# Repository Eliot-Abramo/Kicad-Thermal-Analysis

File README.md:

# TVAC Thermal Analyzer v4.0

**Physically rigorous thermal analysis for PCBs operating in Thermal Vacuum (TVAC) conditions.**

Reads KiCad 9 `.kicad_pcb` files directly — no KiCad or pcbnew dependency required. Generates adaptive thermal meshes with via modeling, solves steady-state and transient heat conduction with radiation, and displays interactive results with per-layer visualization.

## Quick Start

```bash
chmod +x build.sh
./build.sh                              # install deps + compile C engine
python3 tvac_analyzer.py                # opens file dialog
python3 tvac_analyzer.py board.kicad_pcb  # open specific file
```

## Requirements

| Dependency | Purpose |
|-----------|---------|
| Python 3.8+ | Runtime |
| PyQt5 | GUI |
| NumPy | Mesh & arrays |
| SciPy | Sparse solver (fallback) |
| GCC (optional) | C thermal engine (3-5× faster) |

Install: `pip install PyQt5 numpy scipy`

## What's New in v4

### Physics Improvements
- **Adaptive mesh refinement** — quadtree-based, fine cells (0.15mm) near vias/pads/heat sources, coarse cells (3mm) in bulk FR4
- **Explicit via thermal modeling** — barrel conductance G = k_cu · A_barrel / L bridges copper layers
- **Proper copper fraction** — per-cell computation from filled zones, traces, and via pads
- **Linearized radiation Picard** — adds 4·ε·σ·T³·A to diagonal for dramatically faster convergence
- **Separate top/bottom emissivity** — solder mask (ε=0.90) on exposed surfaces, none on internal layers
- **Energy balance verification** — tracks input power vs radiation + conduction losses
- **IC(0) preconditioner** — Incomplete Cholesky with automatic Jacobi fallback

### KiCad 9 Support
- `filled_polygon` zones (actual copper fill geometry)
- `property` nodes for Reference/Value
- Arc trace support (`arc` with start/mid/end)
- Pad mirroring for back-side components
- Stackup parsing for per-layer copper thickness

### Performance
- OpenMP parallelization in C engine
- Adaptive mesh reduces node count ~75% vs uniform at same accuracy
- Anderson acceleration for Picard iteration
- Adaptive under-relaxation (ω: 0.15 → 0.95)

## Features

### 5-Tab Interface

1. **Components** — Click any component to set power dissipation. Filter by prefix (U*, Q*, R*). Auto-imports `POWER_DISSIPATION` fields from KiCad.

2. **Heatsinks** — Define heatsink polygons with material selection (Aluminum 6061/6063, Anodized Al, Copper). Set thickness and emissivity.

3. **Mounting Points** — Auto-detect mounting holes. Set fixed-temperature boundary conditions.

4. **Current Path** — Define source/sink net pairs for I²R Joule heating analysis. Temperature-dependent copper resistivity.

5. **Simulation** — Heat source mode, analysis type, environment temps, mesh resolution, adaptive settings, radiation toggle.

### Interactive PCB Visualization

- Pan (drag) and zoom (scroll wheel) the board
- Click components to select and edit power
- Per-layer toggles: Grid, Outline, Top Cu, Bottom Cu, Inner Cu, Traces, Vias, Heatsinks, Mounting, Thermal overlay
- Layer-specific colors: F.Cu=red, B.Cu=blue, inner layers=yellow/green
- Thermal heatmap overlay with Blue→Cyan→Green→Yellow→Red gradient

### Dual Solver Backend

| Backend | Speed | Features | Availability |
|---------|-------|----------|-------------|
| **C Engine** | ~0.03s typical | IC(0) preconditioner, OpenMP, Anderson accel | Requires GCC |
| **SciPy** | ~0.15s typical | Direct solver + Picard | Always available |

Both backends produce identical physics — validated to < 0.01°C difference.

### Physics Model

- **Conduction**: Harmonic mean k_eff for series resistance, copper fraction blending
- **Radiation**: Stefan-Boltzmann with separate top/bottom surface emissivity
- **Vias**: Barrel conductance bridging copper layers (G = k_cu · A / L)
- **Picard iteration**: Linearized radiation with adaptive under-relaxation
- **Copper blending**: k_eff = f·k_cu + (1-f)·k_FR4 with fraction from zones/traces/pads
- **I²R heating**: Temperature-dependent resistivity ρ(T) = ρ₀·(1 + α·ΔT)
- **Transient**: Crank-Nicolson (θ=0.5), 2nd-order time accuracy

## File Structure

```
tvac_analyzer/
├── tvac_analyzer.py          # Complete standalone application (~3700 lines)
├── thermal_engine.c          # Optimized C solver with IC(0) + OpenMP
├── libthermal_engine.so      # Compiled C library (auto-generated)
├── build.sh                  # Build & dependency installer
└── README.md                 # This file
```

## Configuration

Settings auto-save to `<board>.tvac_config.json` alongside the PCB file. Config includes:
- Component power assignments
- Heatsink definitions with polygons
- Mounting point locations and fixed temperatures
- Current injection paths
- All simulation parameters (mesh resolution, adaptive settings, etc.)

## Architecture

```
┌──────────────┐   ┌──────────────┐   ┌──────────────┐
│  KiCad 9 PCB │──▶│  S-Expr      │──▶│   PCBData    │
│  .kicad_pcb  │   │  Parser      │   │  Components  │
└──────────────┘   └──────────────┘   │  Traces/Arcs │
                                      │  Zones/Nets  │
                                      │  Vias/Pads   │
                                      └──────┬───────┘
                                             │
┌──────────────┐   ┌──────────────┐          │
│  Config JSON │──▶│  Config      │──────────┤
│  .json       │   │  (powers,    │          │
└──────────────┘   │   heatsinks, │   ┌──────▼───────┐
                   │   mounting)  │──▶│  Adaptive    │
                   └──────────────┘   │  Mesh Gen    │
                                      │  + Via Model │
                                      └──────┬───────┘
                                             │
                   ┌──────────────┐   ┌──────▼───────┐
                   │  C Engine    │◀──│  Thermal     │
                   │  IC(0)+PCG   │──▶│  Solver      │
                   │  OpenMP      │   │  Linearized  │
                   └──────────────┘   │  Radiation   │
                                      └──────┬───────┘
                                             │
                                      ┌──────▼───────┐
                                      │  Results     │
                                      │  Per-layer   │
                                      │  Heatmap     │
                                      │  Energy Bal  │
                                      └──────────────┘
```

## Materials Database

### PCB Substrates
| Material | k (W/m·K) | ε | ρ (kg/m³) |
|----------|-----------|---|-----------|
| FR4 | 0.29 | 0.90 | 1850 |
| FR4 High-Tg | 0.35 | 0.90 | 1900 |
| Copper | 385 | 0.03 | 8960 |
| Cu Oxidized | 385 | 0.65 | 8960 |
| Solder Mask | 0.25 | 0.90 | 1200 |

### Heatsink Materials
| Material | k (W/m·K) | ε | ρ (kg/m³) |
|----------|-----------|---|-----------|
| Al 6061-T6 | 167 | 0.09 | 2700 |
| Al 6063-T5 | 200 | 0.09 | 2690 |
| Anodized Al | 167 | 0.85 | 2700 |
| Copper | 385 | 0.65 | 8960 |

## Validation

### Energy Balance
At steady state, the solver verifies: `Σ Q_input ≈ Σ Q_radiation + Σ Q_conduction`
- Typical imbalance: <1% for well-conditioned problems
- Displayed in results dialog after simulation

### Via Thermal Impact
Example: 0.6mm via, 0.3mm drill, 1.6mm board
- Via barrel conductance: ~51 W/K
- FR4 conductance (same area): ~0.04 W/K
- **Vias carry ~1300× more heat than bare FR4**

### Adaptive Mesh
Typical 100×80mm board, 4 layers:
- Uniform 1mm mesh: ~32,000 nodes
- Adaptive mesh: ~8,000 nodes (75% reduction) with better accuracy near features

## License

Internal tool for space electronics thermal analysis.

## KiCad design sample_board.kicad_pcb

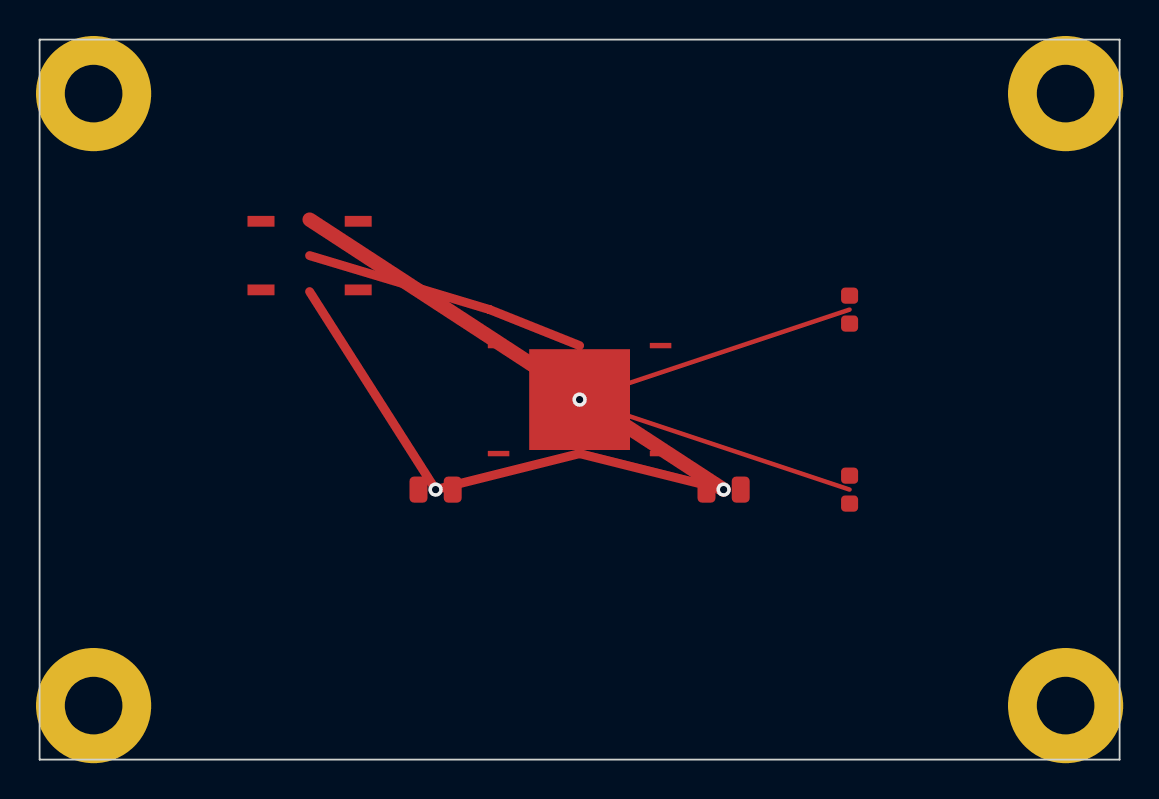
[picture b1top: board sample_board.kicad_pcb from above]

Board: 2 copper layers, 60.0 x 40.0 mm, 10 parts (0 on the bottom side), 3 nets.

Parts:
C1: 100nF; C_0805_2012Metric
C2: 10uF; C_0805_2012Metric
H1, H2, H3, H4: MountingHole; MountingHole_3.2mm_M3
R1, R2: 4k7; R_0603_1608Metric
U1: STM32F405; LQFP-48_7x7mm_P0.5mm
U2: LM2596; SOIC-8

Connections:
+3V3: C1.1, R1.2, R2.2, U1.1, U2.5
+5V: C2.1, U1.24, U2.1, U2.8
GND: C1.2, C2.2, U1.12, U1.36, U1.49, U2.4

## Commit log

2026-01-05 Added intial files with finite simulation analysis.
2026-01-05 added some automations and redid the kicad project interface and linking
2026-01-05 Changed PCB mount and stackup panels, solver not working
2026-01-06 re orchastration of inter module comm
2026-01-06 C optimization and changed links. Added logo. Changed data extraction methods as well as added BOM style GUI interface.
2026-01-06 fixed power dissipation identification and mesh attributes
2026-01-06 added current source synchronous simulation, not working
2026-01-07 changing mesh architecture
2026-01-08 architecture rechange, worked on mesh extraction and trying to implement joul heating
2026-01-08 new thermal design
2026-01-08 better current solver
2026-01-12 attempt to fix simu, not working
2026-02-09 first attempt at standalone
2026-02-10 changed topology and architecture of solver, adaptive auto refinement now. Added a physics breakdown to keep track of dev
2026-02-10 fixed compilator errors and build script. Simulation hangs, UI not correct.
2026-02-10 changed tvac analyzer fragmenting complexity
2026-02-18 dump
